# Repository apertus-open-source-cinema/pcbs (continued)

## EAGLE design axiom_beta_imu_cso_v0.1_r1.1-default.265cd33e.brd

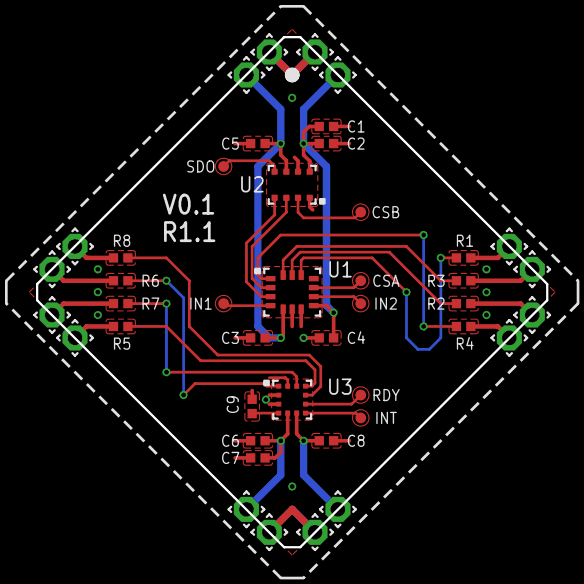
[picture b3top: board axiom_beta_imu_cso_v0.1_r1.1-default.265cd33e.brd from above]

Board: 2 copper layers, 28.3 x 28.3 mm, 44 parts (1 on the bottom side), 31 nets.

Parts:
C1, C7: 1u; 0402-C
C2, C3, C4, C5, C6, C8, C9: 100n; 0402-C
CSA: TPTP06R; TP06R
CSB: TPTP06R; TP06R
IN1, IN2: TPTP06R; TP06R
INT: TPTP06R; TP06R
LOGO1: OSHW_LOGO_FILLX0100-NT; OSHW_FILLX100_NOTEXT
R1, R2, R3, R4, R5, R6, R7, R8: 0402-C
RDY: TPTP06R; TP06R
SDO: TPTP06R; TP06R
U1: LSM6DS3H; LGA-14L
U2: DPS310; VLGA-8
U3: LIS3MDL; VFLGA-12
U$1, U$2, U$3, U$4, U$5, U$6, U$7, U$8, U$9, U$10, U$11, U$12, U$13, U$14, U$15, U$16: PINPAD2.00MM; 1.4/0.8

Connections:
CSO_NE_V: C1.1, C2.1, C4.1, U1.8, U2.8, U$4.1
CSO_NW_V: C3.1, C5.1, U1.5, U2.6, U$3.1
CSO_SE_V: C8.1, U3.6, U$14.1
CSO_SW_V: C6.1, C7.1, U3.5, U$13.1
C_CK_E: R2.1, U$10.1
C_CK_W: R6.1, U$7.1
C_EN_E: R1.1, U$6.1
C_EN_W: R5.1, U$11.1
C_SI_E: R3.1, U$8.1
C_SI_W: R7.1, U$9.1
C_SO_E: R4.1, U$12.1
C_SO_W: R8.1, U$5.1
GND: C1.2, C2.2, C3.2, C4.2, C5.2, C6.2, C7.2, C8.2, C9.2, U1.6, U1.7, U2.1, U2.7, U3.2, U3.3, U3.12, U$1.1, U$2.1, U$15.1, U$16.1
unnamed: U1.3, U2.4
unnamed: U1.2, U2.3
unnamed: IN2.TP, U1.9
unnamed: CSA.TP, U1.10
unnamed: IN1.TP, U1.4
unnamed: SDO.TP, U2.5
unnamed: CSB.TP, U2.2
unnamed: INT.TP, U3.7
unnamed: RDY.TP, U3.8
unnamed: C9.1, U3.4
N_CS: R1.2, U1.12
N_SDI: R3.2, U1.14
N_SDO: R4.2, U1.1
N_SPC: R2.2, U1.13
S_CS: R5.2, U3.10
S_SDI: R7.2, U3.11
S_SDO: R8.2, U3.9
S_SPC: R6.2, U3.1

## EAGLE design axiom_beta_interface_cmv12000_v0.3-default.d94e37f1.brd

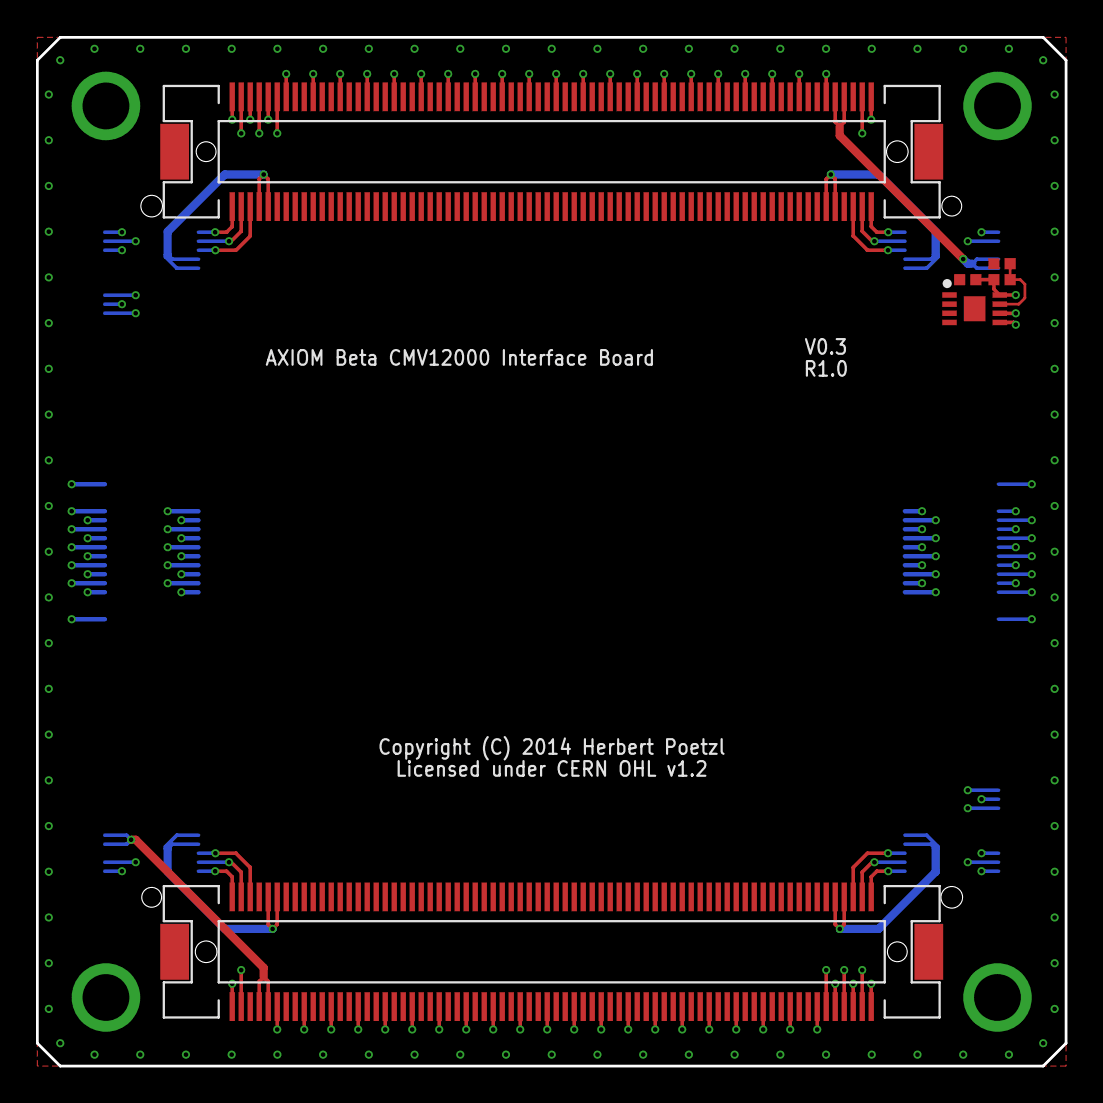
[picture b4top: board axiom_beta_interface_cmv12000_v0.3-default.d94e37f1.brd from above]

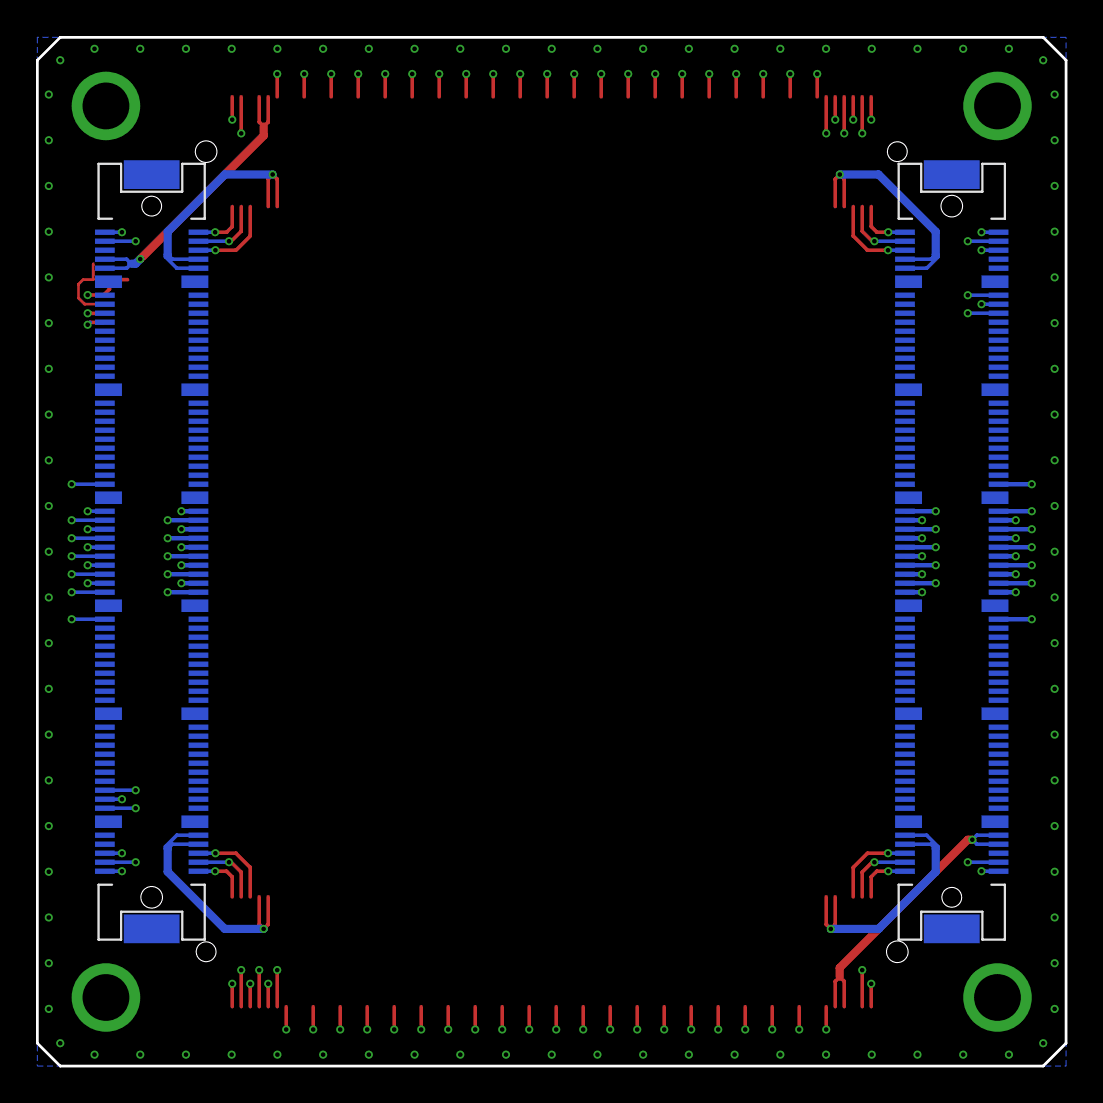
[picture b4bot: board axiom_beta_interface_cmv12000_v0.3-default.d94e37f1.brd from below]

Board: 4 copper layers, 57.1 x 57.1 mm, 10 parts (2 on the bottom side), 50 nets.

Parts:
C1: 0402-B
PARALLELLA: PARALLELLA-FRAME
R1, R2: 0402-B
U1: BR24G04NUX; DFN200X300X100-9N
U$1: µZ-FRAME
X-EAST: FX10-120/12P; FX10A-120P/12
X-NORTH: FX10-144S; FX10A-144S
X-SOUTH: FX10-144S; FX10A-144S
X-WEST: FX10-120/12P; FX10A-120P/12

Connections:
E_I2C_V: C1.1, R1.1, U1.8, X-EAST.11, X-EAST.13
E_JTAG_V: X-EAST.19, X-EAST.21
E_SCL: U1.6, X-EAST.15
E_SDA: U1.5, X-EAST.17
E_VE: X-EAST.99, X-EAST.101, X-EAST.103, X-EAST.104, X-EAST.106, X-EAST.108
GND: C1.2, R2.2, U1.1, U1.2, U1.3, U1.4, U1.EP, X-EAST.5, X-EAST.20, X-EAST.23, X-EAST.26, X-EAST.29, X-EAST.32, X-EAST.35, X-EAST.38, X-EAST.41, X-EAST.44, X-EAST.47, X-EAST.50, X-EAST.72, X-EAST.73, X-EAST.78, X-EAST.79, X-EAST.84, X-EAST.85, X-EAST.90, X-EAST.91, X-EAST.96, X-EAST.97, X-EAST.102, X-EAST.G1, X-EAST.G2, X-EAST.G3, X-EAST.G4, X-EAST.G5, X-EAST.G6, X-EAST.G7, X-EAST.G8, X-EAST.G9, X-EAST.G10, X-EAST.G11, X-EAST.G12, X-NORTH.11, X-NORTH.17, X-NORTH.23, X-NORTH.29, X-NORTH.35, X-NORTH.41, X-NORTH.47, X-NORTH.53, X-NORTH.59, X-NORTH.65, X-NORTH.71, X-NORTH.77, X-NORTH.83, X-NORTH.89, X-NORTH.95, X-NORTH.101, X-NORTH.107, X-NORTH.113, X-NORTH.119, X-NORTH.125, X-NORTH.131, X-NORTH.137, X-NORTH.140, X-SOUTH.11, X-SOUTH.17, X-SOUTH.23, X-SOUTH.29, X-SOUTH.35, X-SOUTH.41, X-SOUTH.47, X-SOUTH.53, X-SOUTH.59, X-SOUTH.65, X-SOUTH.71, X-SOUTH.77, X-SOUTH.83, X-SOUTH.89, X-SOUTH.95, X-SOUTH.101, X-SOUTH.107, X-SOUTH.113, X-SOUTH.119, X-SOUTH.125, X-SOUTH.131, X-SOUTH.137, X-SOUTH.140, X-WEST.5, X-WEST.20, X-WEST.23, X-WEST.26, X-WEST.29, X-WEST.32, X-WEST.35, X-WEST.38, X-WEST.41, X-WEST.44, X-WEST.47, X-WEST.50, X-WEST.72, X-WEST.73, X-WEST.78, X-WEST.79, X-WEST.84, X-WEST.85, X-WEST.90, X-WEST.91, X-WEST.96, X-WEST.97, X-WEST.102, X-WEST.G1, X-WEST.G2, X-WEST.G3, X-WEST.G4, X-WEST.G5, X-WEST.G6, X-WEST.G7, X-WEST.G8, X-WEST.G9, X-WEST.G10, X-WEST.G11, X-WEST.G12
unnamed: R1.2, R2.1, U1.7
N_CHK_V: X-NORTH.7, X-NORTH.9, X-WEST.112, X-WEST.114
N_I2C_V: X-EAST.7, X-EAST.9, X-NORTH.136, X-NORTH.138
N_SCK: X-EAST.2, X-NORTH.143
N_SCL: X-EAST.1, X-NORTH.144
N_SDA: X-EAST.3, X-NORTH.142
N_SDI: X-EAST.6, X-NORTH.139
N_SDO: X-EAST.4, X-NORTH.141
N_SPI_V: X-EAST.8, X-EAST.10, X-NORTH.133, X-NORTH.135
N_VE: X-EAST.49, X-EAST.51, X-EAST.53, X-EAST.55, X-EAST.57, X-EAST.59, X-NORTH.104, X-NORTH.110, X-NORTH.116, X-NORTH.122, X-NORTH.128, X-NORTH.134
N_VE_CV: X-NORTH.5, X-WEST.116
N_VE_OV: X-NORTH.6, X-WEST.115
N_VE_UV: X-NORTH.12, X-WEST.105
N_VN: X-NORTH.50, X-NORTH.56, X-NORTH.62, X-NORTH.68, X-NORTH.74, X-NORTH.80, X-NORTH.86, X-NORTH.92, X-NORTH.98, X-WEST.52, X-WEST.54, X-WEST.56, X-WEST.58, X-WEST.60, X-WEST.62, X-WEST.64, X-WEST.66, X-WEST.68, X-WEST.70
N_VN_CV: X-NORTH.3, X-WEST.118
N_VN_OV: X-NORTH.4, X-WEST.117
N_VN_UV: X-NORTH.10, X-WEST.107
N_VW: X-NORTH.14, X-NORTH.20, X-NORTH.26, X-NORTH.32, X-NORTH.38, X-NORTH.44, X-WEST.61, X-WEST.63, X-WEST.65, X-WEST.67, X-WEST.69, X-WEST.71
N_VW_CV: X-NORTH.1, X-WEST.120
N_VW_OV: X-NORTH.2, X-WEST.119
N_VW_UV: X-NORTH.8, X-WEST.109
S_CHK_V: X-EAST.112, X-EAST.114, X-SOUTH.7, X-SOUTH.9
S_I2C_V: X-SOUTH.136, X-SOUTH.138, X-WEST.7, X-WEST.9
S_SCK: X-SOUTH.143, X-WEST.2
S_SCL: X-SOUTH.144, X-WEST.1
S_SDA: X-SOUTH.142, X-WEST.3
S_SDI: X-SOUTH.139, X-WEST.6
S_SDO: X-SOUTH.141, X-WEST.4
S_SPI_V: X-SOUTH.133, X-SOUTH.135, X-WEST.8, X-WEST.10
S_VE: X-EAST.61, X-EAST.63, X-EAST.65, X-EAST.67, X-EAST.69, X-EAST.71, X-SOUTH.14, X-SOUTH.20, X-SOUTH.26, X-SOUTH.32, X-SOUTH.38, X-SOUTH.44
S_VE_CV: X-EAST.120, X-SOUTH.1
S_VE_OV: X-EAST.119, X-SOUTH.2
S_VE_UV: X-EAST.109, X-SOUTH.8
S_VS: X-EAST.52, X-EAST.54, X-EAST.56, X-EAST.58, X-EAST.60, X-EAST.62, X-EAST.64, X-EAST.66, X-EAST.68, X-EAST.70, X-SOUTH.50, X-SOUTH.56, X-SOUTH.62, X-SOUTH.68, X-SOUTH.74, X-SOUTH.80, X-SOUTH.86, X-SOUTH.92, X-SOUTH.98
S_VS_CV: X-EAST.118, X-SOUTH.3
S_VS_OV: X-EAST.117, X-SOUTH.4
S_VS_UV: X-EAST.107, X-SOUTH.10
S_VW: X-SOUTH.104, X-SOUTH.110, X-SOUTH.116, X-SOUTH.122, X-SOUTH.128, X-SOUTH.134, X-WEST.49, X-WEST.51, X-WEST.53, X-WEST.55, X-WEST.57, X-WEST.59
S_VW_CV: X-EAST.116, X-SOUTH.5
S_VW_OV: X-EAST.115, X-SOUTH.6
S_VW_UV: X-EAST.105, X-SOUTH.12
W_I2C_V: X-WEST.11, X-WEST.13
W_SDI_V: X-WEST.19, X-WEST.21
W_VW: X-WEST.99, X-WEST.101, X-WEST.103, X-WEST.104, X-WEST.106, X-WEST.108

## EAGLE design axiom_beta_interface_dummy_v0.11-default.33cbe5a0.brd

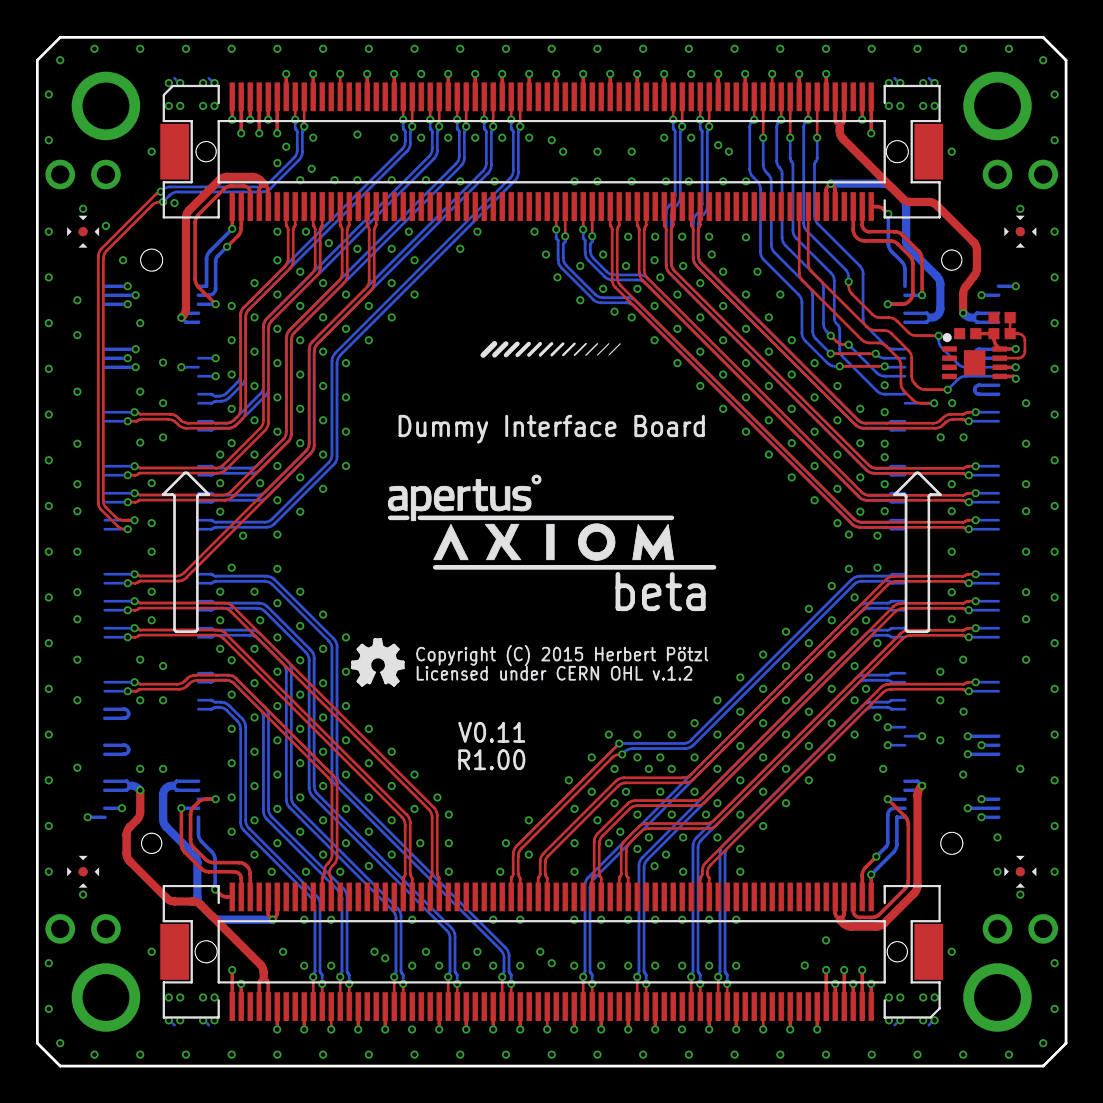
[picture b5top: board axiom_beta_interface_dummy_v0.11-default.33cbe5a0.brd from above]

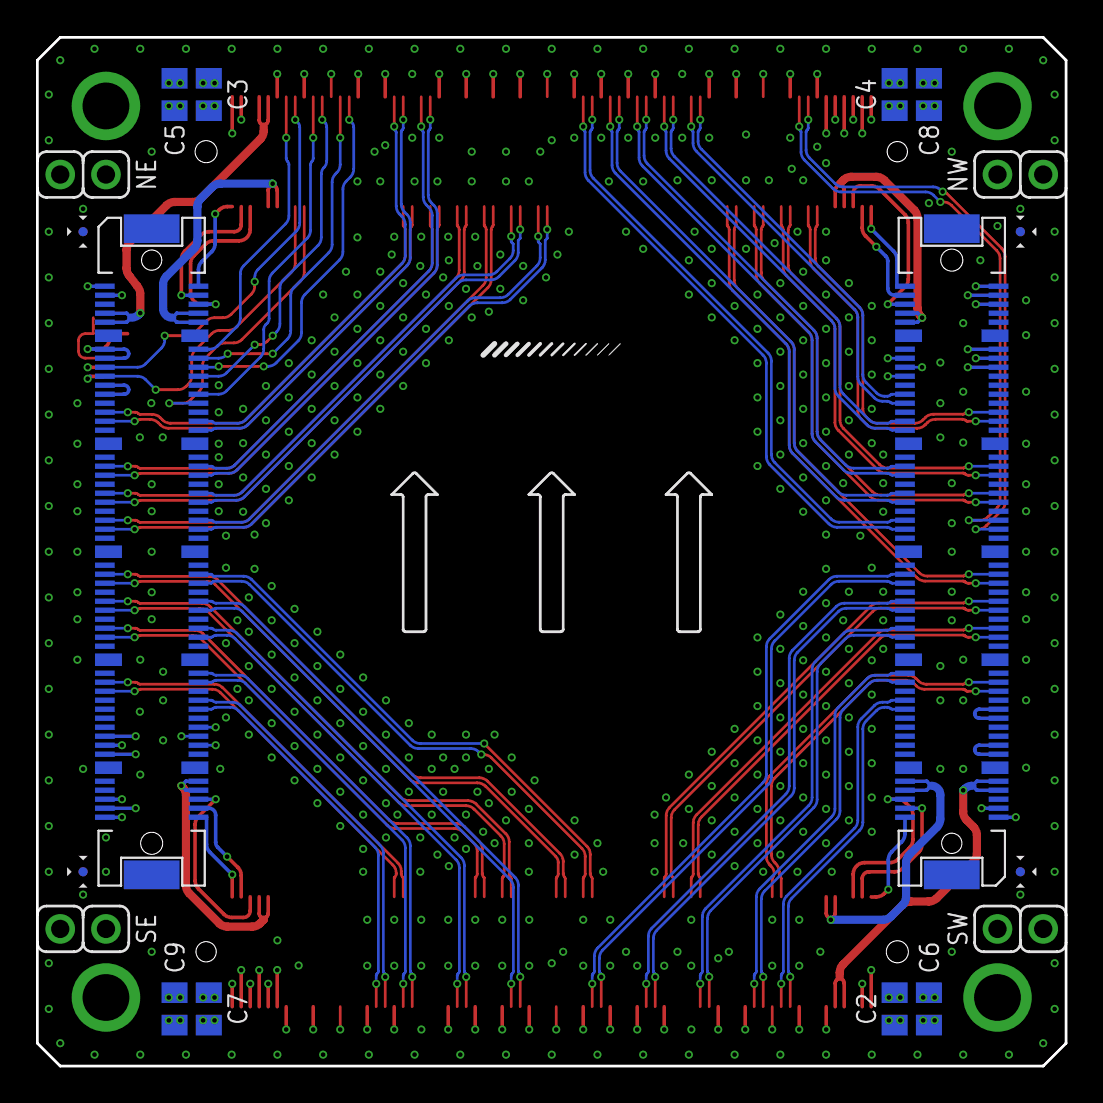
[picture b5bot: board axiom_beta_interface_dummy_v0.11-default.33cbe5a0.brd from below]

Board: 4 copper layers, 57.1 x 57.1 mm, 25 parts (14 on the bottom side), 132 nets.

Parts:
C1: 0402-B
C2, C3, C4, C5, C6, C7, C8, C9: 0805-B
LOGO1: OSHW_LOGO_FILLX0100-NT; OSHW_FILLX100_NOTEXT
NE: 1X02
NW: 1X02
PARALLELLA: PARALLELLA-FRAME
R1, R2: 0402-B
SE: 1X02
SW: 1X02
U1: BR24G04NUX; DFN200X300X100-9N
U$1: µZ-FRAME
U$2: APERTUS_LOGO334X100; APERTUS_LOGO_334X100
U$3: AXIOM_LOGO525X80; AXIOM_LOGO_525X80
X-EAST: FX10-100/10P; FX10A-100P/10
X-NORTH: FX10-144S; FX10A-144S
X-SOUTH: FX10-144S; FX10A-144S
X-WEST: FX10-100/10P; FX10A-100P/10

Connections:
CLK_IN: X-EAST.24, X-NORTH.128
E_I2C_V: C1.1, R1.1, U1.8, X-EAST.11, X-EAST.13
E_SDI_V: X-EAST.19, X-EAST.21
E_VE: C9.1, SE.2
FRAME_REQ: X-EAST.15, X-NORTH.129
GND: C1.2, C2.2, C3.2, C4.2, C5.2, C6.2, C7.2, C8.2, C9.2, R2.2, U1.1, U1.2, U1.3, U1.4, U1.EP, X-EAST.5, X-EAST.20, X-EAST.23, X-EAST.26, X-EAST.29, X-EAST.31, X-EAST.32, X-EAST.37, X-EAST.38, X-EAST.43, X-EAST.44, X-EAST.49, X-EAST.50, X-EAST.51, X-EAST.52, X-EAST.57, X-EAST.58, X-EAST.63, X-EAST.64, X-EAST.69, X-EAST.70, X-EAST.71, X-EAST.76, X-EAST.77, X-EAST.82, X-EAST.G1, X-EAST.G2, X-EAST.G3, X-EAST.G4, X-EAST.G5, X-EAST.G6, X-EAST.G7, X-EAST.G8, X-EAST.G9, X-EAST.G10, X-NORTH.12, X-NORTH.18, X-NORTH.24, X-NORTH.30, X-NORTH.36, X-NORTH.42, X-NORTH.43, X-NORTH.48, X-NORTH.54, X-NORTH.60, X-NORTH.66, X-NORTH.72, X-NORTH.78, X-NORTH.84, X-NORTH.90, X-NORTH.96, X-NORTH.102, X-NORTH.103, X-NORTH.108, X-NORTH.114, X-NORTH.120, X-NORTH.126, X-NORTH.132, X-NORTH.138, X-NORTH.139, X-SOUTH.12, X-SOUTH.18, X-SOUTH.24, X-SOUTH.30, X-SOUTH.36, X-SOUTH.42, X-SOUTH.43, X-SOUTH.48, X-SOUTH.54, X-SOUTH.60, X-SOUTH.66, X-SOUTH.72, X-SOUTH.78, X-SOUTH.84, X-SOUTH.90, X-SOUTH.96, X-SOUTH.102, X-SOUTH.103, X-SOUTH.108, X-SOUTH.114, X-SOUTH.120, X-SOUTH.126, X-SOUTH.132, X-SOUTH.138, X-SOUTH.139, X-WEST.5, X-WEST.20, X-WEST.23, X-WEST.26, X-WEST.29, X-WEST.31, X-WEST.32, X-WEST.37, X-WEST.38, X-WEST.43, X-WEST.44, X-WEST.49, X-WEST.50, X-WEST.51, X-WEST.52, X-WEST.57, X-WEST.58, X-WEST.63, X-WEST.64, X-WEST.69, X-WEST.70, X-WEST.71, X-WEST.76, X-WEST.77, X-WEST.82, X-WEST.G1, X-WEST.G2, X-WEST.G3, X-WEST.G4, X-WEST.G5, X-WEST.G6, X-WEST.G7, X-WEST.G8, X-WEST.G9, X-WEST.G10
JTAG_V: X-WEST.19, X-WEST.21
LVDS_CLK_N: X-NORTH.14, X-WEST.75
LVDS_CLK_P: X-NORTH.16, X-WEST.73
unnamed: R1.2, R2.1, U1.7
N_CHK_V: X-NORTH.8, X-NORTH.10, X-WEST.92, X-WEST.94
N_I2C_V: X-EAST.7, X-EAST.9, X-NORTH.135, X-NORTH.137
N_SCK: X-EAST.2, X-NORTH.144
N_SCL: X-EAST.1, X-NORTH.143
N_SDA: X-EAST.3, X-NORTH.141
N_SDI: X-EAST.6, X-NORTH.140
N_SDO: X-EAST.4, X-NORTH.142
N_SPI_V: X-EAST.8, X-EAST.10, X-NORTH.134, X-NORTH.136
N_VE: C5.1, NE.2, X-NORTH.109, X-NORTH.115, X-NORTH.127, X-NORTH.133
N_VE_CV: X-NORTH.6, X-WEST.96
N_VE_OV: X-NORTH.5, X-WEST.95
N_VE_RS: X-NORTH.121, X-WEST.88
N_VE_UV: X-NORTH.11, X-WEST.85
N_VN: C3.1, NE.1, X-NORTH.49, X-NORTH.55, X-NORTH.61, X-NORTH.67, X-NORTH.79, X-NORTH.85, X-NORTH.91, X-NORTH.97
N_VN_CV: X-NORTH.4, X-WEST.98
N_VN_OV: X-NORTH.3, X-WEST.97
N_VN_RS: X-NORTH.73, X-WEST.86
N_VN_UV: X-NORTH.9, X-WEST.87
N_VW: C4.1, NW.1, X-NORTH.13, X-NORTH.19, X-NORTH.31, X-NORTH.37
N_VW_CV: X-NORTH.2, X-WEST.100
N_VW_OV: X-NORTH.1, X-WEST.99
N_VW_RS: X-NORTH.25, X-WEST.84
N_VW_UV: X-NORTH.7, X-WEST.89
OUT1_N: X-SOUTH.119, X-WEST.28
OUT1_P: X-SOUTH.117, X-WEST.30
OUT3_N: X-SOUTH.124, X-WEST.25
OUT3_P: X-SOUTH.122, X-WEST.27
OUT5_N: X-SOUTH.107, X-WEST.34
OUT5_P: X-SOUTH.105, X-WEST.36
OUT7_N: X-SOUTH.106, X-WEST.33
OUT7_P: X-SOUTH.104, X-WEST.35
OUT9_N: X-SOUTH.95, X-WEST.40
OUT9_P: X-SOUTH.93, X-WEST.42
OUT11_N: X-SOUTH.100, X-WEST.39
OUT11_P: X-SOUTH.98, X-WEST.41
OUT13_N: X-SOUTH.83, X-WEST.46
OUT13_P: X-SOUTH.81, X-WEST.48
OUT15_N: X-EAST.54, X-SOUTH.82
OUT15_P: X-EAST.56, X-SOUTH.80
OUT17_N: X-EAST.53, X-SOUTH.76
OUT17_P: X-EAST.55, X-SOUTH.74
OUT19_N: X-EAST.60, X-SOUTH.65
OUT19_P: X-EAST.62, X-SOUTH.63
OUT21_N: X-EAST.59, X-SOUTH.64
OUT21_P: X-EAST.61, X-SOUTH.62
OUT23_N: X-EAST.66, X-SOUTH.53
OUT23_P: X-EAST.68, X-SOUTH.51
OUT25_N: X-EAST.65, X-SOUTH.58
OUT25_P: X-EAST.67, X-SOUTH.56
OUT27_N: X-EAST.73, X-SOUTH.40
OUT27_P: X-EAST.75, X-SOUTH.38
OUT29_N: X-EAST.72, X-SOUTH.41
OUT29_P: X-EAST.74, X-SOUTH.39
OUT31_N: X-EAST.78, X-SOUTH.35
OUT31_P: X-EAST.80, X-SOUTH.33
OUT33_N: X-NORTH.20, X-WEST.67
OUT33_P: X-NORTH.22, X-WEST.65
OUT35_N: X-NORTH.26, X-WEST.61
OUT35_P: X-NORTH.28, X-WEST.59
OUT37_N: X-NORTH.32, X-WEST.47
OUT37_P: X-NORTH.34, X-WEST.45
OUT39_N: X-NORTH.39, X-WEST.80
OUT39_P: X-NORTH.41, X-WEST.78
OUT41_N: X-NORTH.45, X-WEST.74
OUT41_P: X-NORTH.47, X-WEST.72
OUT43_N: X-NORTH.51, X-WEST.68
OUT43_P: X-NORTH.53, X-WEST.66
OUT45_N: X-NORTH.57, X-WEST.62
OUT45_P: X-NORTH.59, X-WEST.60
OUT47_N: X-NORTH.63, X-WEST.56
OUT47_P: X-NORTH.65, X-WEST.54
OUT49_N: X-EAST.48, X-NORTH.74
OUT49_P: X-EAST.46, X-NORTH.76
OUT51_N: X-EAST.42, X-NORTH.80
OUT51_P: X-EAST.40, X-NORTH.82
OUT53_N: X-EAST.47, X-NORTH.86
OUT53_P: X-EAST.45, X-NORTH.88
OUT55_N: X-EAST.41, X-NORTH.92
OUT55_P: X-EAST.39, X-NORTH.94
OUT57_N: X-EAST.35, X-NORTH.98
OUT57_P: X-EAST.33, X-NORTH.100
OUT59_N: X-EAST.27, X-NORTH.104
OUT59_P: X-EAST.25, X-NORTH.106
OUT61_N: X-EAST.36, X-NORTH.99
OUT61_P: X-EAST.34, X-NORTH.101
OUT63_N: X-EAST.30, X-NORTH.105
OUT63_P: X-EAST.28, X-NORTH.107
OUTCLK_N: X-NORTH.15, X-WEST.53
OUTCLK_P: X-NORTH.17, X-WEST.55
OUTCTR_N: X-SOUTH.125, X-WEST.22
OUTCTR_P: X-SOUTH.123, X-WEST.24
SPI_EN: X-EAST.14, X-NORTH.119
SYS_RES_N: X-EAST.22, X-NORTH.125
S_CHK_V: X-EAST.92, X-EAST.94, X-SOUTH.8, X-SOUTH.10
S_I2C_V: X-SOUTH.135, X-SOUTH.137, X-WEST.7, X-WEST.9
S_SCK: X-SOUTH.144, X-WEST.2
S_SCL: X-SOUTH.143, X-WEST.1
S_SDA: X-SOUTH.141, X-WEST.3
S_SDI: X-SOUTH.140, X-WEST.6
S_SDO: X-SOUTH.142, X-WEST.4
S_SPI_V: X-SOUTH.134, X-SOUTH.136, X-WEST.8, X-WEST.10
S_VE: C7.1, SE.1, X-SOUTH.13, X-SOUTH.19, X-SOUTH.31, X-SOUTH.37
S_VE_CV: X-EAST.100, X-SOUTH.2
S_VE_OV: X-EAST.99, X-SOUTH.1
S_VE_RS: X-EAST.84, X-SOUTH.25
S_VE_UV: X-EAST.89, X-SOUTH.7
S_VS: C6.1, SW.1, X-SOUTH.49, X-SOUTH.55, X-SOUTH.61, X-SOUTH.67, X-SOUTH.79, X-SOUTH.85, X-SOUTH.91, X-SOUTH.97
S_VS_CV: X-EAST.98, X-SOUTH.4
S_VS_OV: X-EAST.97, X-SOUTH.3
S_VS_RS: X-EAST.86, X-SOUTH.73
S_VS_UV: X-EAST.87, X-SOUTH.9
S_VW: C2.1, SW.2, X-SOUTH.109, X-SOUTH.115, X-SOUTH.127, X-SOUTH.133
S_VW_CV: X-EAST.96, X-SOUTH.6
S_VW_OV: X-EAST.95, X-SOUTH.5
S_VW_RS: X-EAST.88, X-SOUTH.121
S_VW_UV: X-EAST.85, X-SOUTH.11
TDIG1: X-EAST.18, X-NORTH.123
TDIG2: X-EAST.17, X-NORTH.130
T_EXP1: X-EAST.12, X-NORTH.131
T_EXP2: X-EAST.16, X-NORTH.117
W_I2C_V: X-WEST.11, X-WEST.13
W_VW: C8.1, NW.2
